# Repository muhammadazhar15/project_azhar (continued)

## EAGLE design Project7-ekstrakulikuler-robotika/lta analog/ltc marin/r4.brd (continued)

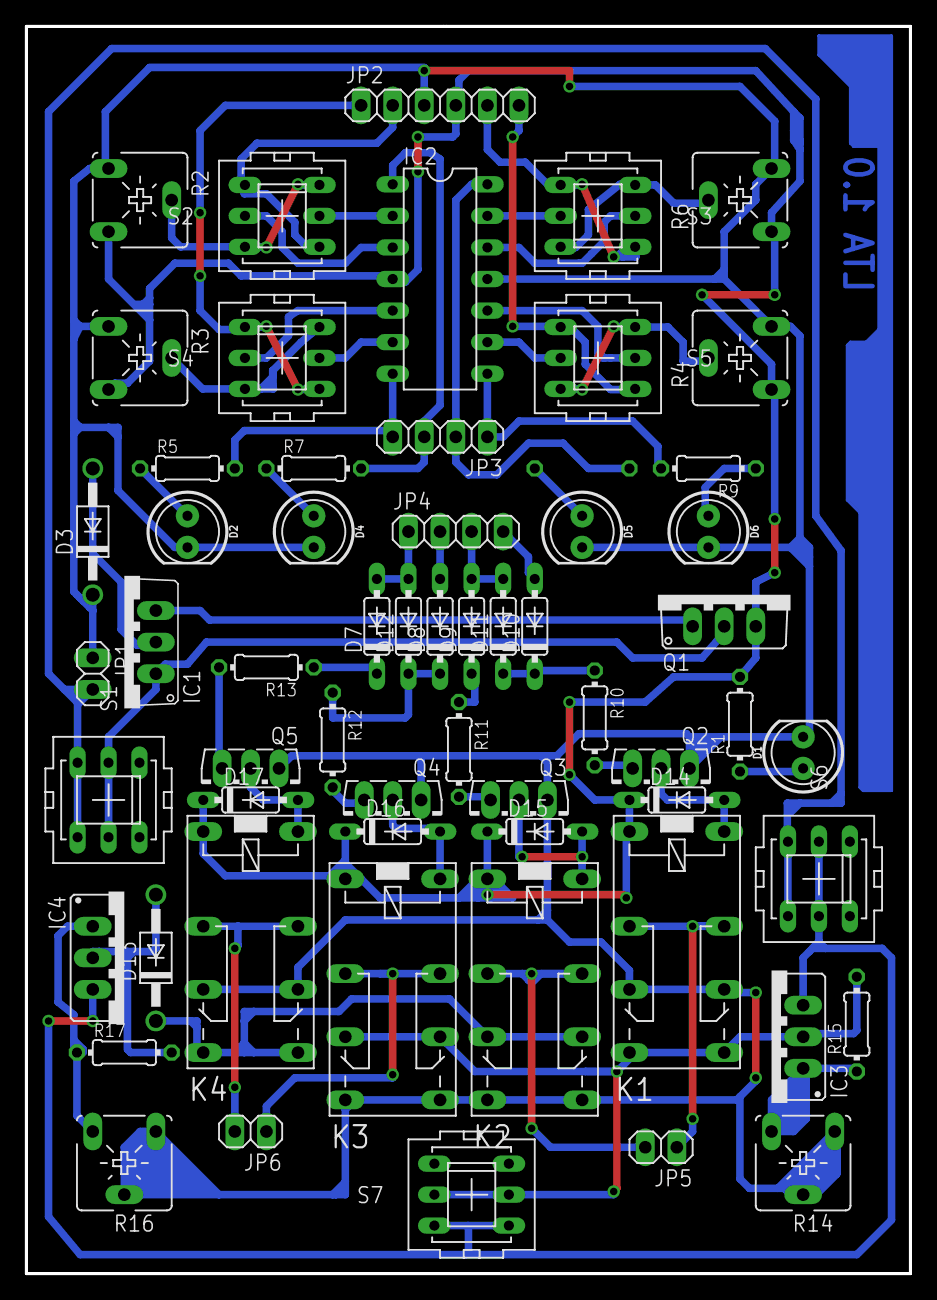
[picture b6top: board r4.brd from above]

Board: 2 copper layers, 71.1 x 100.3 mm, 60 parts (1 on the bottom side), 57 nets.

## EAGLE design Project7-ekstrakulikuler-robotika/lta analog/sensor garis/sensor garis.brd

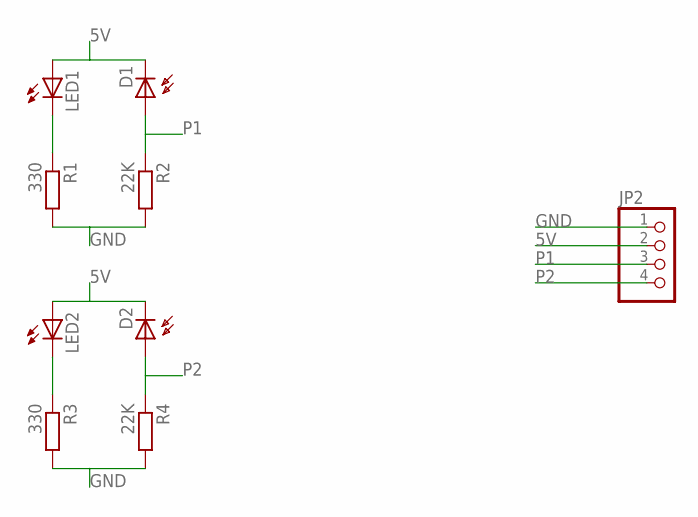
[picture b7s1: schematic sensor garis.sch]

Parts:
D1, D2: BPX65
JP2: PINHD-1X4; 1X04
LED1, LED2: LED3MM
R1, R3: 330; 0207/7
R2, R4: 22K; 0207/7

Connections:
5V: D1.K (C), D2.K (C), JP2.2, LED1.A, LED2.A
GND: JP2.1, R1.2, R2.2, R3.2, R4.2
unnamed: LED2.K (C), R3.1
unnamed: LED1.K (C), R1.1
P1: D1.A, JP2.3, R2.1
P2: D2.A, JP2.4, R4.1

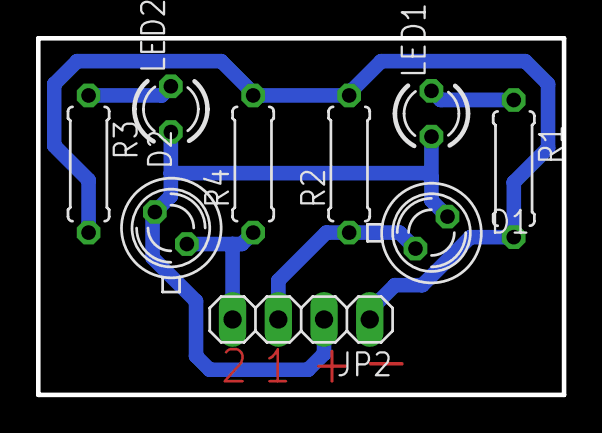
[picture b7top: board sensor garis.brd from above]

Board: 2 copper layers, 29.2 x 19.8 mm, 9 parts (0 on the bottom side), 6 nets.

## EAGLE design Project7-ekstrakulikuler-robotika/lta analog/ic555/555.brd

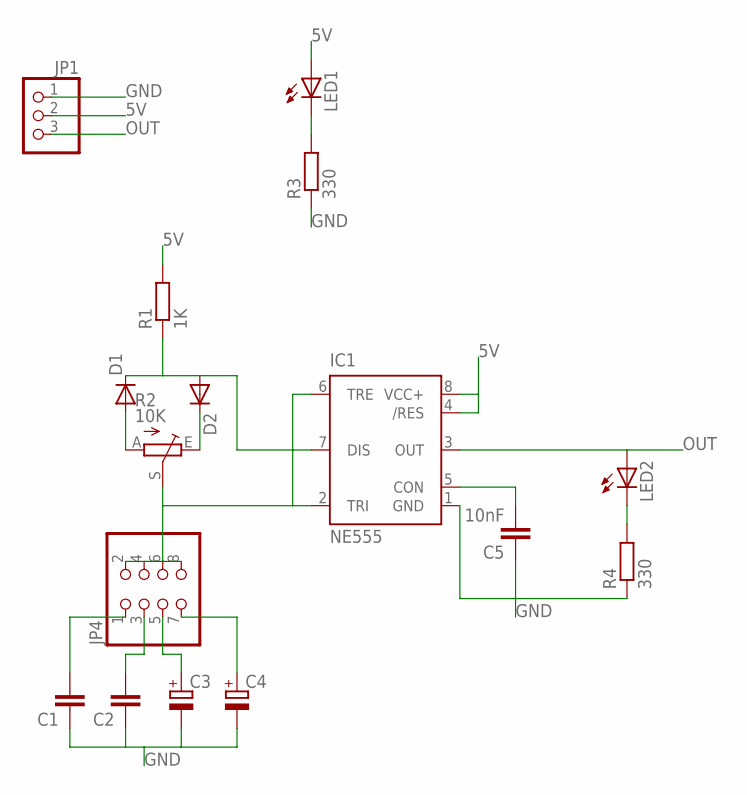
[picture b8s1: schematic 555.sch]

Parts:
C1, C2: C-EU025-030X050; C025-030X050
C3, C4: CPOL-EUE2.5-6; E2,5-6
C5: 10nF; C025-030X050
D1, D2: 1N4148DO35-7; DO35-7
IC1: NE555; DIL-08
JP1: PINHD-1X3; 1X03
JP4: PINHD-2X4; 2X04
LED1, LED2: LED3MM
R1: 1K; 0207/7
R2: 10K; CA6V
R3, R4: 330; 0207/7

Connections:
5V: IC1.4 (/RES), IC1.8 (VCC+), JP1.2, LED1.A, R1.2
GND: C1.1, C2.1, C3.-, C4.-, C5.1, IC1.1 (GND), JP1.1, R3.1, R4.1
unnamed: LED1.K (C), R3.2
unnamed: C5.2, IC1.5 (CON)
unnamed: IC1.2 (TRI), IC1.6 (TRE), JP4.2, JP4.4, JP4.6, JP4.8, R2.S
unnamed: D1.C, D2.A, IC1.7 (DIS), R1.1
unnamed: D1.A, R2.A
unnamed: D2.C, R2.E
unnamed: C1.2, JP4.1
unnamed: C4.+, JP4.7
unnamed: C2.2, JP4.3
unnamed: C3.+, JP4.5
unnamed: LED2.K (C), R4.2
OUT: IC1.3 (OUT), JP1.3, LED2.A

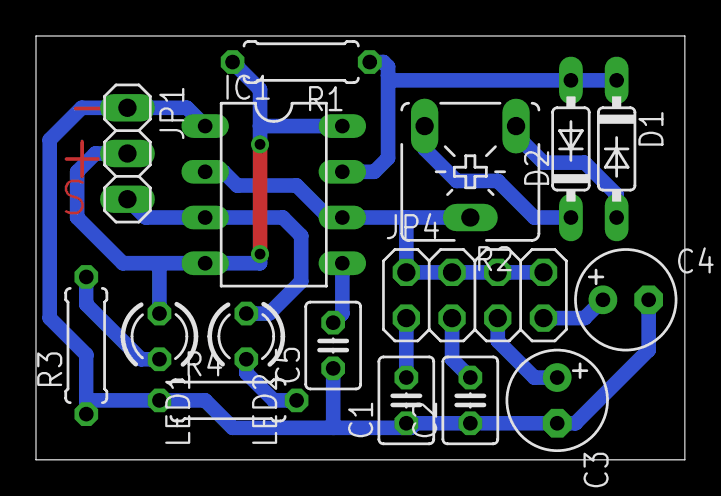
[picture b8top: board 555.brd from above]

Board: 2 copper layers, 36.0 x 23.5 mm, 16 parts (0 on the bottom side), 14 nets.

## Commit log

2023-01-17 Create txt
2023-01-17 Update and rename txt to readme
2023-01-17 Create r
2023-01-17 Update and rename r to readme
2023-01-17 Rename Project3-pendeteksi-penyakit-jantung/readme to Project3-pendeteksi_penyakit_jantung/readme
2023-01-21 Create Test_data
2023-01-21 Rename Project1-robot_localization/Data_pengujian/readme to Project1-robot_localization/Test_data/readme
2023-01-21 test
2023-01-21 Renamed_file
2023-01-22 rename
2023-01-22 rename file
2023-01-22 add file
2023-05-30 add folder
2023-05-30 remove folder
2023-05-30 edit file
